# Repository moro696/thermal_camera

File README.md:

# thermal_camera
A diy thermal camera based on a Flir Lepton 3.5 sensor

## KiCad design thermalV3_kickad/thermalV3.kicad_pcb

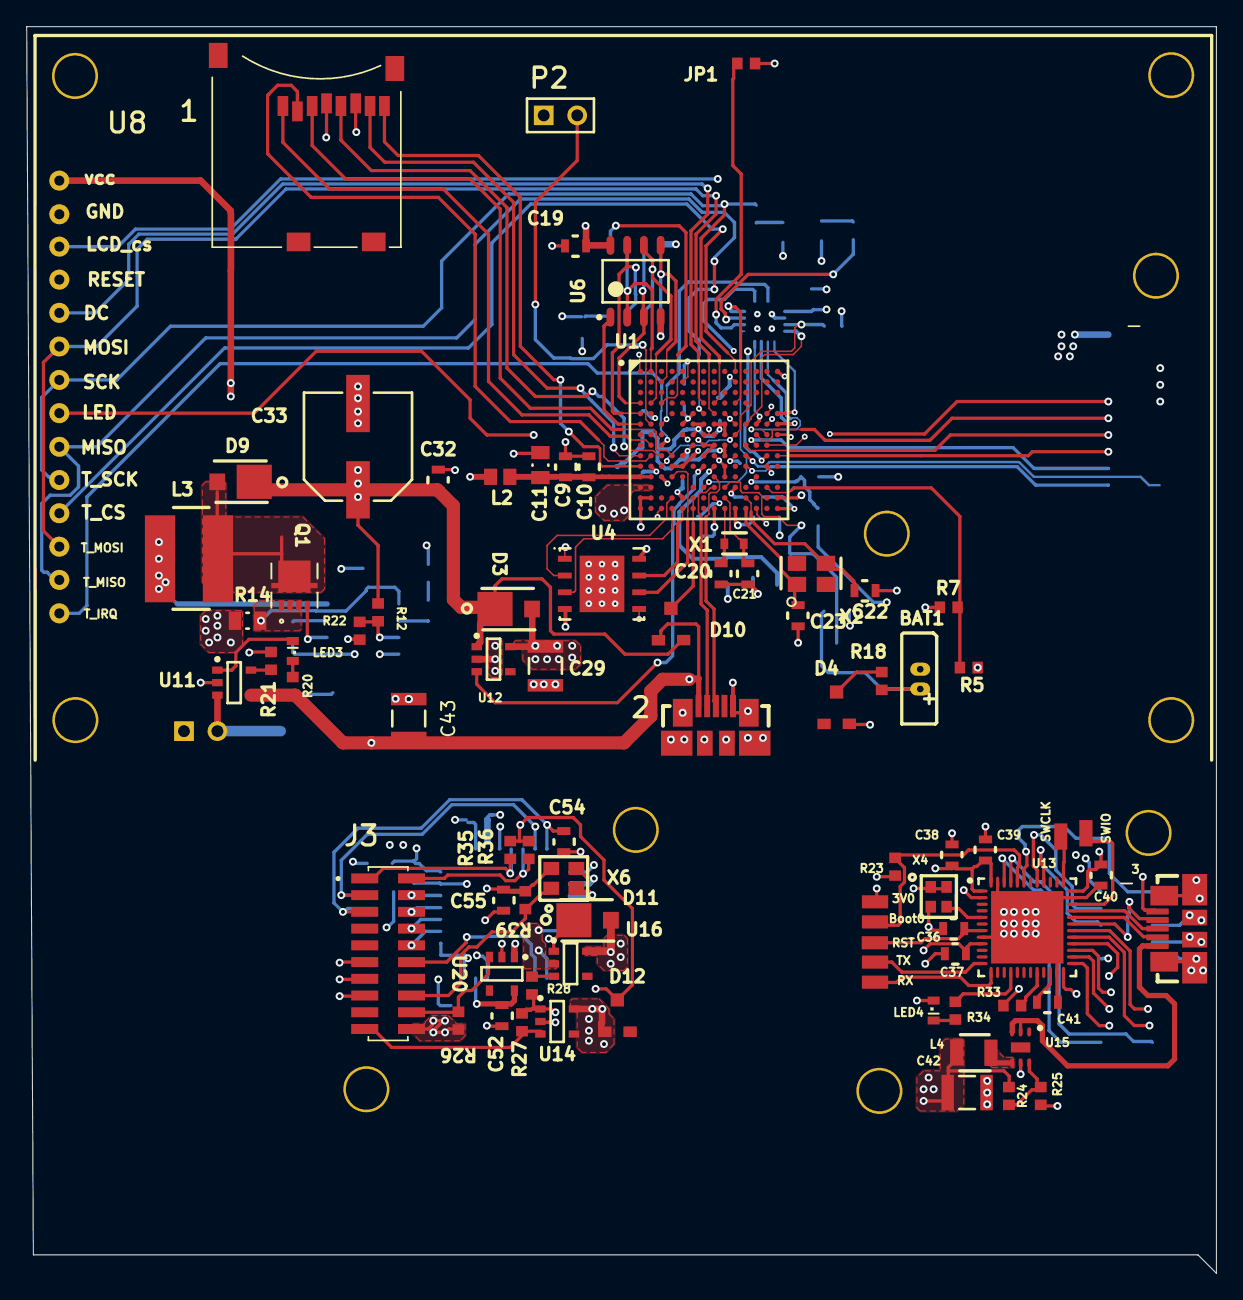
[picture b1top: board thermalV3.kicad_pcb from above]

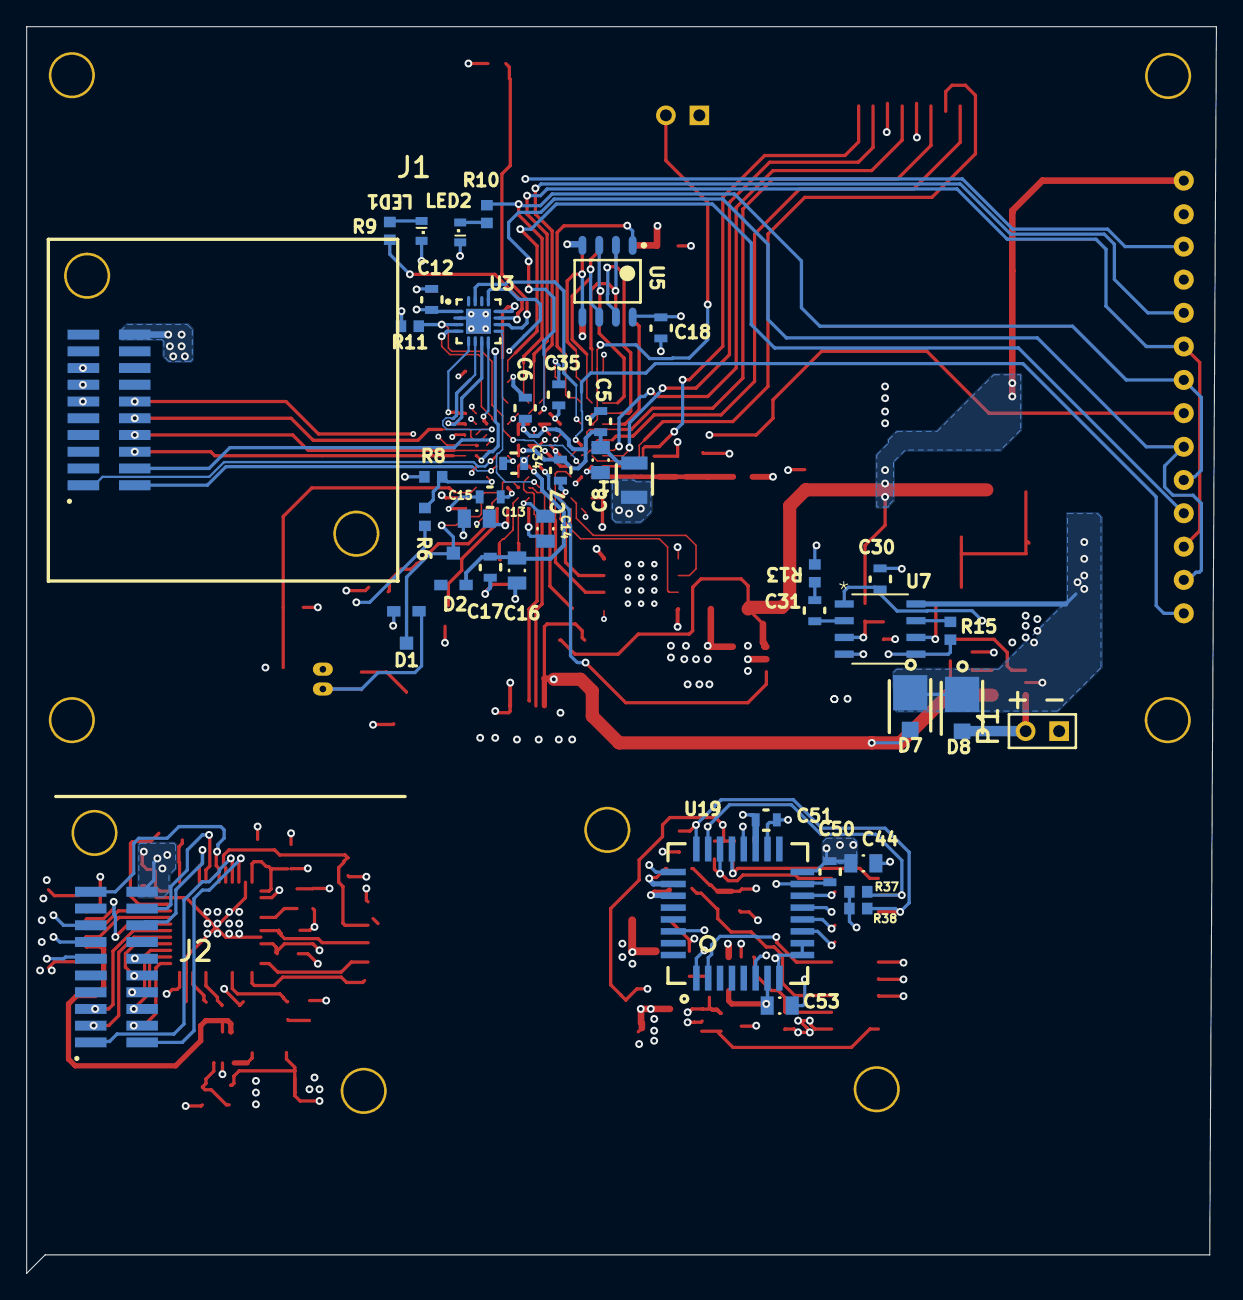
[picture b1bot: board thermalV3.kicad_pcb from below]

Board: 4 copper layers, 90.3 x 94.6 mm, 124 parts (42 on the bottom side), 133 nets.

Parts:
1: SF-MICROSD; MICROSD
2, 3: USB-B-AB-MICRO-B-SMT; MOLEX-47346-0001
3V0: testpoint; solderPad
BAT1: MS621FE-FL11E; MS621FE-FL11E - duplicate
Boot0: testpoint; solderPad
C5, C6, C7, C9, C10, C12, C15, C17, C18, C19, C20, C21, C22, C23, C30, C31, C32, C34, C35, C36, C37, C38, C39, C40, C41, C50, C51, C52, C54, C55: 0603; CAP0603new
C8, C11, C13, C14, C16, C44, C53: 0805; CAP0805new
C29, C42: 1210; CAP1210
C33: 33u35v; CAPAE33u35v
C43: CAP1210
D1, D2, D4, D10, D12: BAT54C; SOT23
D3, D7, D8, D9, D11: DO220; DO-220AA
J1, J2: cam_brd_top; cam_board_top
J3: 20021321-00020C4LF; AMPHENOL_20021321-00020C4LF
JP1: 0603; RES0603new
L1, L4: LQH2HPN4R7MDRL
L2: Inductor0805; INDC0805
L3: LPS6235-123MRC
LED1, LED2, LED3, LED4: 0603; 0603-LED
P1: battery; HDR1X2
P2: button; HDR1X2
Q1: STL11N3LLH6; POWERFLAT-3p3X3p3_STM
R5, R6, R7, R8, R9, R10, R11, R12, R13, R15, R18, R20, R21, R22, R23, R24, R25, R26, R27, R28, R33, R34, R35, R36, R37, R38, R39: 0603; RES0603new
R14: 0805; RES0805new
RST: testpoint; solderPad
RX: testpoint; solderPad
SWCLK: swclk; solderPad
SWIO: swdio; solderPad
TX: testpoint; solderPad
U1: MIMXRT1062DVJ6B
U3: MKL02Z32VFG4; QFN16
U4: W25Q64JVZPIM; WSON6_6x5mm
U5, U6: APS6404L-3SQR-SN; SOP8
U7: LM3478MA/NOPB; M08A
U8: 3.2INCH DISPLAY; 3.2DISPLAY
U11: MCP73832T-2DCI/OT; SOT23-5
U12: TLV75733PDBVR; SOT23-5
U13: STM32F401CBU6; QFN50P700X700X60_HS-49N
U14, U16: TLV75528PDBVR; SOT23-5
U15: PAM2305DGFADJ; DFN2x2
U19: Lepton Flir 3.5 sensor; Molex_ 105028_1001
U20: NCP114ASN120T1G; SOT23-5
X1: QT1C-32.768KDZB-T; Quartz1.6x0.8
X2: TSX-3225 24.0000MF15X-AC3
X4: MP007043
X6: SIT1602BI-13-28E-25.000000

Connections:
1V2_core_brd: C52.2, C53.2, U19.7, U20.5
3V3: 1.4, C12.1, C18.2, C19.2, C29.2, C34.2, C35.2, D1.2, D3.2, D4.2, J1.2, L2.1, LED1.A, P2.1, U1.E6, U1.E9, U1.F5, U1.F10, U1.J6, U1.J10, U1.K4, U1.K5, U1.N14, U1.P12, U3.1, U4.8, U5.8, U6.8, U8.4, U12.5
3V3_brd: D11.1, D12.3, J3.20, R26.2, R27.2, R28.1, R35.2, R36.2, U14.1, U16.1, U20.1
+2V8_brd: C51.1, C55.2, D12.1, R37.1, R38.1, R39.1, U14.5, U19.19, X6.4
+2V8_shutter_brd: C44.2, C50.2, D11.2, U16.5, U19.16
+5V: C32.2, C33.1, D3.1, D9.1, D10.2, R12.2, U8.1, U12.1
BL_ON_OFF: U1.H13, U8.8
BUCK_ON: J2.4, U13.41
BUCK_ON_BRD: J3.18, R26.1, U20.3
GND: 1.6, 2.GND, 2.GND1, 2.GND2, 2.GND3, 2.GND4, 2.GND5, 2.GND6, 3.GND, 3.GND1, 3.GND2, 3.GND3, 3.GND4, 3.GND5, 3.GND6, BAT1.2, C5.1, C6.1, C7.1, C8.1, C9.2, C10.2, C11.2, C12.2, C13.1, C14.1, C15.1, C16.1, C17.1, C18.1, C19.1, C20.2, C21.2, C22.2, C23.2, C29.1, C30.2, C32.1, C33.2, C34.1, C35.1, C36.1, C37.1, C38.1, C39.1, C40.1, C41.2, C42.1, C43.2, C44.1, C50.1, C51.2, C52.1, C53.1, C54.1, C55.1, J1.2, J1.5, J1.7, J1.9, J2.5, J2.7, J2.9, J3.11, J3.13, J3.15, JP1.1, LED2.C, P1.1, R7.1, R8.1, R11.1, R13.1, R14.1, R15.1, R21.1, R22.1, R23.1, R25.1, R33.2, U1.A1, U1.A14, U1.B5, U1.B10, U1.E2, U1.E13, U1.G7, U1.G8, U1.G14, U1.H7, U1.H8, U1.J7, U1.J8, U1.K2, U1.K9, U1.K13, U1.L9, U1.N1, U1.N2, U1.N5, U1.N8, U1.P1, U1.P14, U3.2, U3.17, U4.4, U5.4, U6.4, U7.4, U7.5, U8.2, U11.2, U12.2, U13.8, U13.23, U13.35, U13.47, U13.49, U14.2, U15.5, U16.2, U19.1, U19.6, U19.8, U19.9, U19.10, U19.15, U19.18, U19.20, U19.25, U19.27, U19.30, U20.2, X4.2, X6.2
LCD_D/C: U1.D7, U8.5
LCD_chip_select: U1.J13, U8.3
LDO_ON: J2.1, U13.43
LDO_ON_brd: J3.19, R27.1, U14.3
Lipo_Measure: R5.1, R7.2, U1.M13
Net1_1: 1.1, U1.H2
Net1_2: 1.2, U1.J2
Net1_3: 1.3, U1.J4
Net1_5: 1.5, U1.J3
Net1_7: 1.7, U1.J1
Net1_8: 1.8, U1.K1
Net2_D+: 2.D+, U1.L8
Net2_D-: 2.D-, U1.M8
Net3_D+: 3.D+, U13.33
Net3_D-: 3.D-, U13.32
Net3_ID: 3.ID, U13.31
NetC9_1: C9.1, C10.1, C11.1, L2.2, U1.L1, U1.L2
NetC13_2: C13.2, U1.P10
NetC14_2: C14.2, U1.P8
NetC15_2: C15.2, U1.M10
NetC16_2: C16.2, C17.2, D2.2, U1.K8
NetC20_1: C20.1, U1.P9, X1.1
NetC21_1: C21.1, U1.N9, X1.2
NetC22_1: C22.1, U1.N11, X2.3
NetC23_1: C23.1, U1.P11, X2.1
NetC30_1: C30.1, Q1.1, Q1.2, Q1.3, R14.2, U7.1
NetC31_1: C31.1, R13.2
NetC31_2: C31.2, U7.2
NetC41_1: C41.1, U13.22
NetD1_3: D1.3, D2.3, U1.M9
NetD4_3: D4.3, R18.2
NetD9_2: D9.2, L3.1, Q1.5, Q1.6, Q1.7, Q1.8
NetD10_3: D10.3, U1.N6, U1.P6
NetJP1_2: JP1.2, U3.10
NetL1_2: L1.2, U1.M1, U1.M2
NetL4_1: L4.1, U15.4
NetLED1_C: LED1.C, R9.2
NetLED2_A: LED2.A, R10.1
NetLED3_A: LED3.A, R20.1
NetLED3_C: LED3.C, U11.1
NetLED4_C: LED4.C, R34.2
NetQ1_4: Q1.4, U7.6
NetR9_1: R9.1, U3.11
NetR11_2: R11.2, U1.G10, U1.K3, U3.3
NetR12_1: R12.1, R22.2, U7.3
NetR15_2: R15.2, U7.7
NetR21_2: R21.2, U11.5
NetR24_1: R24.1, R25.2, U15.6
NetR28_2: R28.2, U16.3
NetR33_1: R33.1, U13.20
NetTP2_1: SWIO.1, U13.34
NetTP7_1: SWCLK.1, U13.37
NetU1_A2: U1.A2, U5.2, U6.2
NetU1_B3: U1.B3, U5.5, U6.5
NetU1_D1: U1.D1, U5.3, U6.3
NetU1_D2: U1.D2, U5.6, U6.6
NetU1_D3: U1.D3, U5.1
NetU1_D10: U1.D10, U3.12
NetU1_E1: U1.E1, U5.7, U6.7
NetU1_E14: U1.E14, U3.5
NetU1_F1: U1.F1, U6.1
NetU1_F3: U1.F3, U3.15
NetU1_F11: U1.F11, U3.4
NetU1_F12: U1.F12, U3.8
NetU1_F13: U1.F13, U3.13
NetU1_F14: U1.F14, U3.7
NetU1_G13: U1.G13, U3.6
NetU1_K7: U1.K7, U12.3
NetU1_L3: U1.L3, U4.1
NetU1_L4: U1.L4, U4.6
NetU1_M7: U1.M7, U3.9
NetU1_N4: U1.N4, U4.2
NetU1_P3: U1.P3, U4.5
NetU1_P4: U1.P4, U4.3
NetU1_P5: U1.P5, U4.7
NetU13_5: U13.5, X4.3
NetU19_26: U19.26, X6.3
RTP PEN: U1.H3, U8.14
VBAT: BAT1.1, D1.1, R18.1
VDDIO_3V0: 3V0.1, C37.2, C38.2, C39.2, C40.2, C42.2, J2.2, L4.2, LED4.A, R24.2, U13.1, U13.9, U13.24, U13.36, U13.48, X4.1, X4.4
VIN: D8.2, P1.2, R5.2, U11.3
boot0: Boot0.1, R23.2, U13.44
button: P2.2, U1.F2
clk_stby: J2.6, U13.40
clk_stby_brd: J3.16, R39.2, X6.1
disp_miso: U1.E7, U8.9, U8.13
disp_mosi: U1.E8, U8.6, U8.12
disp_sck: R10.2, U1.D8, U8.7, U8.10
flir_clk: J2.16, U13.26
flir_cs: J2.18, U13.25
flir_miso: J2.14, U13.27
flir_mosi: J2.12, U13.28
i2c1_scl: J2.19, U13.45
i2c1_sda: J2.20, U13.46
i2c_scl: J1.19, U1.J11
i2c_scl_brd: J3.1, R35.1, U19.21
i2c_sda: J1.20, U1.K11
i2c_sda_brd: J3.2, R36.1, U19.22
lepton_gpo3: J2.10, U13.2
lepton_pdwn: J2.17, U13.29
lepton_pdwn_brd: J3.3, R37.2, U19.23
lepton_rst: J2.15, U13.30
lepton_rst_brd: C54.2, J3.5, R38.2, U19.24
nrst: C36.2, RST.1, U13.7
pin_touch_cs: U1.A10, U8.11
sensor_gpo_3: J1.10, U1.G5
sensor_gpo_3_brd: J3.12, U19.2
spi_chip_select: J1.18, U1.H12
spi_chip_select_brd: J3.4, U19.14
spi_clk: J1.16, U1.J14
spi_clk_brd: J3.6, U19.13
spi_miso: J1.14, U1.H11
spi_miso_brd: J3.8, U19.12
spi_mosi: J1.12, U1.G12
spi_mosi_brd: J3.3, U19.11
sys_led: R34.1, U13.16
usart2_rx: RX.1, U13.13
usart2_tx: TX.1, U13.12
v_supply: D7.1, D8.1, L3.2, U7.8
v_supply_usb: 3.VBUS, U15.2, U15.3
vsoc: C5.2, C6.2, C7.2, C8.2, L1.1, U1.F6, U1.F7, U1.F8, U1.F9, U1.G6, U1.G9, U1.H6, U1.H9, U1.J5, U1.J9
vusb: 2.VBUS, C43.1, D7.2, D10.1, R6.2, R20.2, U11.4
vusb_measure: R6.1, R8.2, U1.L12

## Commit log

2026-06-23 updated schematic
    updated schematic
2026-06-23 update schematic
2026-06-23 updated pcb footprint
2026-06-23 updated C43 footprint
2026-06-23 project cleanup
2026-06-23 project update
2026-06-23 PDF schematic add
